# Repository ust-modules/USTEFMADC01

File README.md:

# EFMADC01 - Electric Field Mill ADC Module

The **EFMADC01** module is designed to provide an **analog front-end** and **ADC conversion** for [Electric Field Mill sensor](https://github.com/UniversalScientificTechnologies/THUNDERMILL01) development and experiments. It processes analog signals from the field mill electrodes and converts them into digital data for further processing.

## Features

- **High-Precision ADC**: Utilizes the **LTC1865** 16-bit, 250ksps analog-to-digital converter.
- **Low-Noise Analog Front End**: Incorporates **OPA314** operational amplifiers for signal conditioning.
- **Precision and stable Voltage Reference**: Includes a **1.25V reference** for accurate ADC operation.
- **Flexible Power Supply**: Supports **3.3V to 5V** operation.
- **RF Shielding**: Equipped with shielding to reduce external interference.
- **MCX Connector Input**: Enables high-quality signal connection.

## Functional Description

The **EFMADC01** module consists of three main blocks:

1. **Analog Front End (AFE)**:
   - Uses **OPA314** operational amplifiers for signal buffering and amplification.
   - High-impedance resistor (10MΩ) allows direct signal acquisition from the field mill sensor electrodes.

2. **ADC Conversion**:
   - **LTC1865-MS** ADC provides **16-bit resolution** with **250ksps sampling rate**.
   - Accepts differential input signals and supports SPI communication.

3. **Power and Reference**:
   - Powered by an external **3.3V or 5V** supply.
   - Features a **BZV55C-6.2V** Zener diode for overvoltage protection.
   - Uses a **1.25V precision voltage reference** for ADC stability.

## Hardware Connections

### Power Supply:
- **VCC**: Accepts **3.3V to 5V** input.
- **GNDA** and **GND**: Ground connections.

### Analog Input:
- **J9 (MCX Connector)**: Main analog signal input.
- **Operational amplifier stage** conditions the signal before ADC conversion.

## Typical Application

The **EFMADC01** module is primarily used in electric field mill experiments to measure atmospheric electric fields. It can also be employed in low-frequency scientific measurements where high-resolution ADC conversion is required.

## Schematic

For detailed circuit information, please take a look at the [EFMADC01 schematic](/doc/gen/EFMADC01-schematic.pdf) in the documentation.

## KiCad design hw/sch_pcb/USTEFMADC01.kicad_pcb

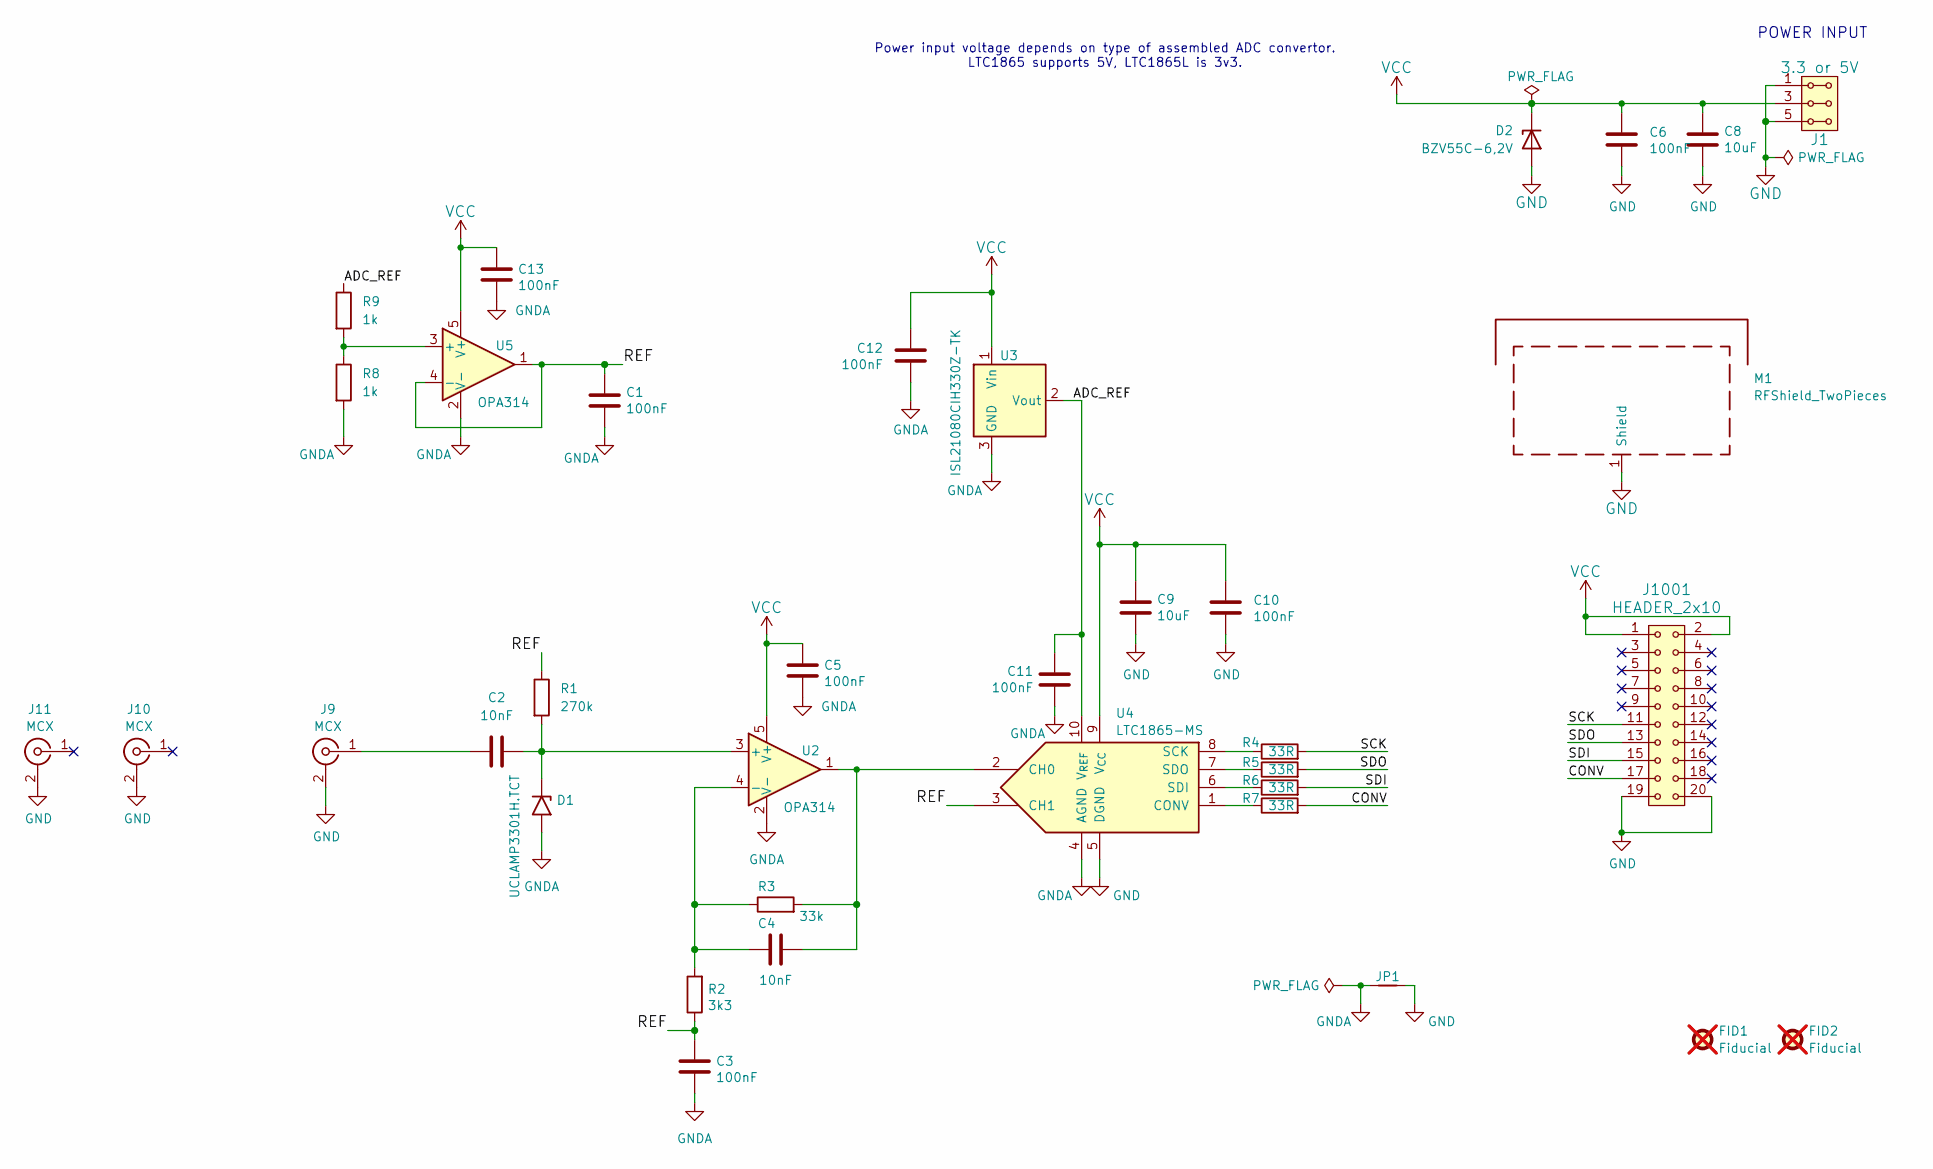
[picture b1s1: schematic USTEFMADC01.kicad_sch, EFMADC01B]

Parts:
C1, C3, C5, C6, C10, C11, C12, C13: 100nF; C_0805_2012Metric
C2, C4: 10nF; C_0805_2012Metric
C8, C9: 10uF; C_0805_2012Metric
D1: UCLAMP3301H.TCT; D_SMB
D2: BZV55C-6,2V; D_MiniMELF
FID1, FID2: Fiducial; Fiducial_1mm_Mask2mm; not fitted
J1: 3.3 or 5V; Straight_2x03
J9, J10, J11: MCX; SMA_Amphenol_901-144_Vertical
J1001: HEADER_2x10; Straight_2x10
JP1: Jumper_2_Bridged; NetTie-2_SMD_Pad0.5mm
M1: RFShield_TwoPieces; Laird_Technologies_BMI-S-204-F_32.00x32.00mm
R1: 270k; R_0805_2012Metric
R2: 3k3; R_0805_2012Metric
R3: 33k; R_0805_2012Metric
R4, R5, R6, R7: 33R; R_0805_2012Metric
R8, R9: 1k; R_0805_2012Metric
U2, U5: OPA314; SOT-23-5
U3: ISL21080CIH330Z-TK; SOT-23
U4: LTC1865-MS; MSOP-10_3x3mm_P0.5mm

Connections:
/ADC_REF: C11.1, R9.1, U3.2 (Vout), U4.10 (V_{REF})
/CONV: J1001.17, R7.2
/REF: C1.1, C3.2, R1.1, R2.1, U4.3 (CH1), U5.1, U5.4 (-)
/SCK: J1001.11, R4.2
/SDI: J1001.15, R6.2
/SDO: J1001.13, R5.2
GND: C6.2, C8.2, C9.2, C10.2, D2.2 (A), J1.1, J1.2, J1.5, J1.6, J9.2 (Ext), J10.2 (Ext_2), J11.2 (Ext_2), J1001.19, J1001.20, JP1.2, M1.1 (Shield_1), U4.5 (DGND)
GNDA: C1.2, C3.1, C5.1, C11.2, C12.2, C13.1, D1.2 (A2), JP1.1, R8.2, U2.2 (V-), U3.3 (GND), U4.4 (AGND), U5.2 (V-)
unnamed: C2.2, D1.1 (A1), R1.2, U2.3 (+)
unnamed: C2.1, J9.1 (In)
unnamed: C4.1, R2.2, R3.1, U2.4 (-)
unnamed: C4.2, R3.2, U2.1, U4.2 (CH0)
unnamed: R7.1, U4.1 (CONV)
unnamed: R4.1, U4.8 (SCK)
unnamed: R6.1, U4.6 (SDI)
unnamed: R5.1, U4.7 (SDO)
unnamed: R8.1, R9.2, U5.3 (+)
VCC: C5.2, C6.1, C8.1, C9.1, C10.1, C12.1, C13.2, D2.1 (K), J1.3, J1.4, J1001.1, J1001.2, U2.5 (V+), U3.1 (Vin), U4.9 (V_{CC}), U5.5 (V+)

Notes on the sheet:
Power input voltage depends on type of assembled ADC convertor. LTC1865 supports 5V, LTC1865L is 3v3.
POWER INPUT

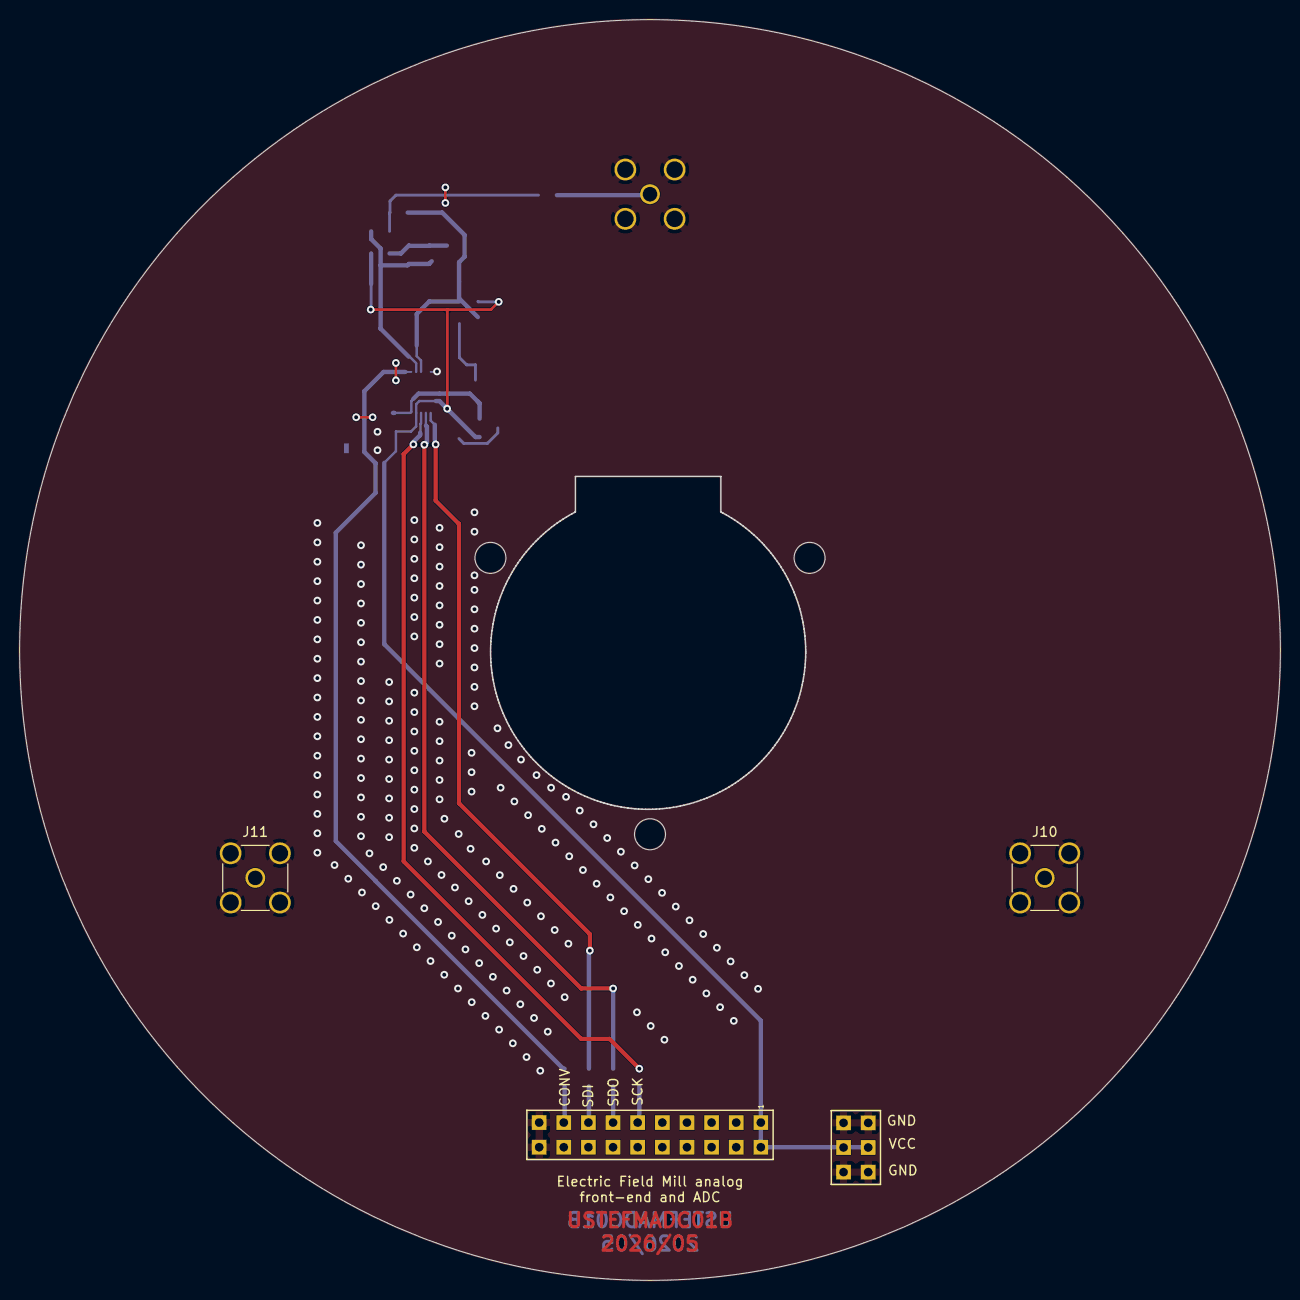
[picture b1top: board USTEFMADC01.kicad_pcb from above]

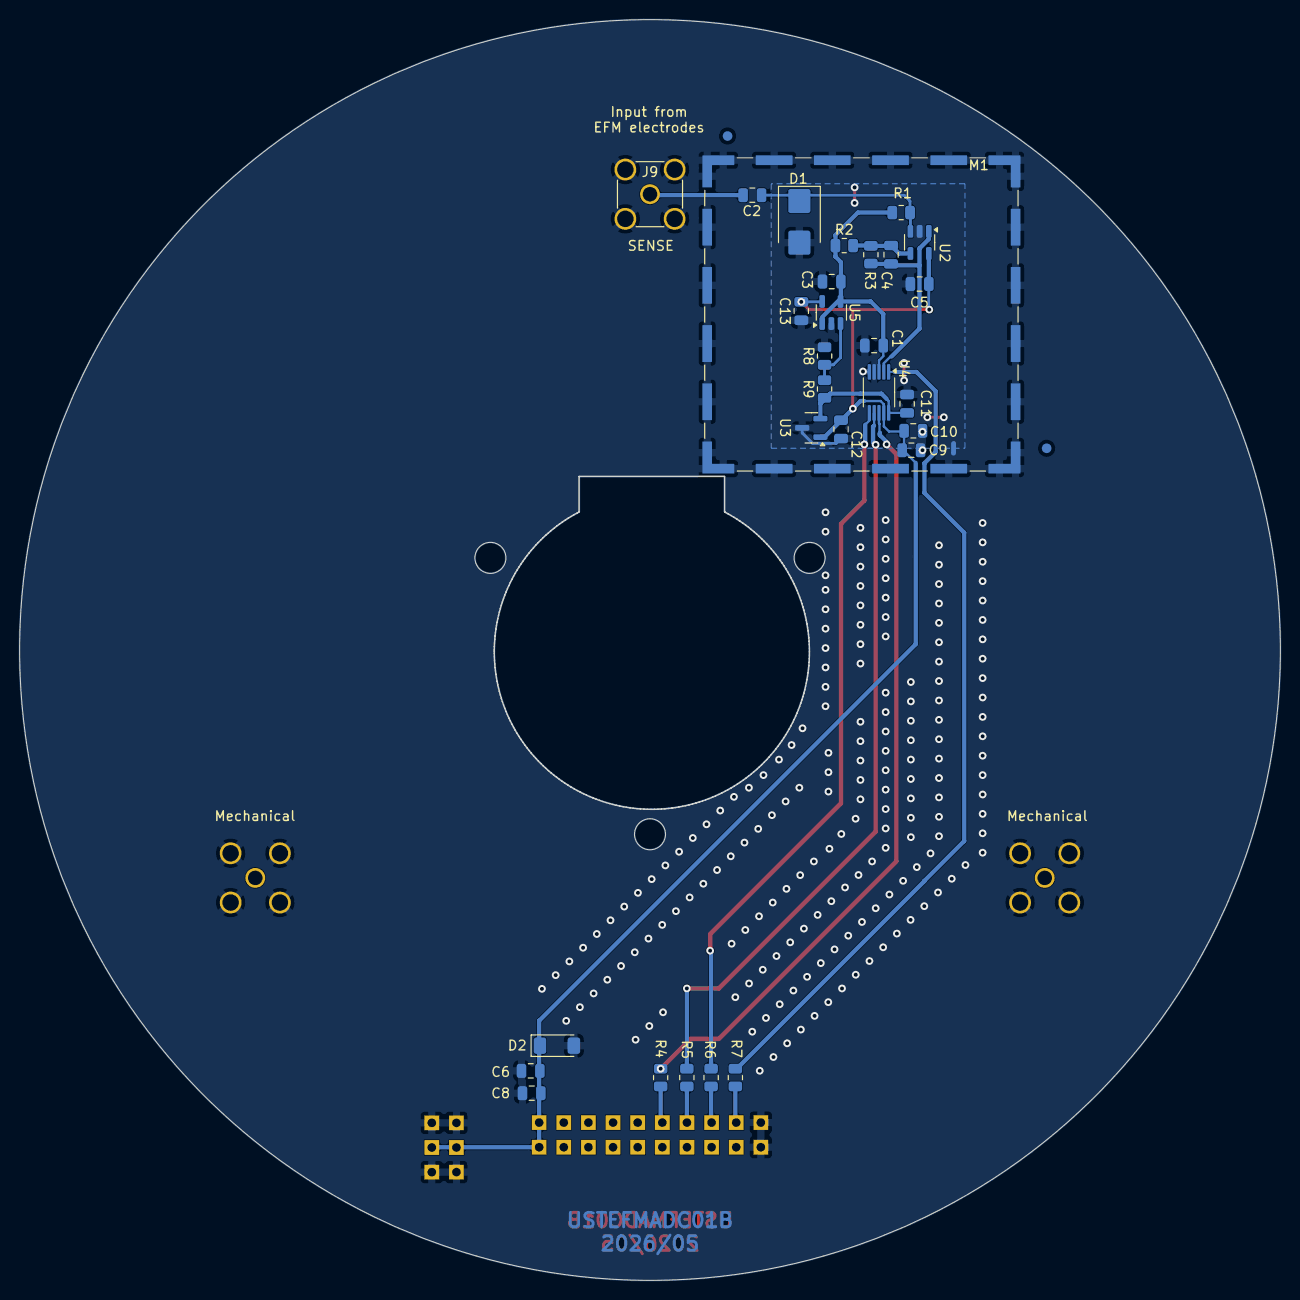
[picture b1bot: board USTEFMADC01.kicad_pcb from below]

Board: 2 copper layers, 129.9 x 129.9 mm, 36 parts (32 on the bottom side), 18 nets.

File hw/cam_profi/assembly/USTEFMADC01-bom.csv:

Component,Description,Part,References,Value,Footprint,Quantity Per PCB,Datasheet,ust_id
1,Unpolarized capacitor,C,C2C4,10nF,C_0805_2012Metric,2,,6508260b462c6d9e720541f1 5c70984812875079b91f8ba6
2,Unpolarized capacitor,C,C1C3C5C6C10C11C12C13,100nF,C_0805_2012Metric,8,,6508260b462c6d9e720541f1 5c70984712875079b91f8b4c
3,Unpolarized capacitor,C,C8C9,10uF,C_0805_2012Metric,2,,5c70984812875079b91f8bbe
4,Zener diode,D_Zener,D2,"BZV55C-6,2V",D_MiniMELF,1,,604b0326128750769e5b0f93
5,"600W unidirectional Transil Transient Voltage Suppressor, 12Vrwm, DO-214AA",SM6T12A,D1,UCLAMP3301H.TCT,D_SMB,1,https://www.st.com/resource/en/datasheet/sm6t.pdf,612514fe1287500165a976f3
6,2x10 2.54 mm pitch header,HEADER_2x10,J1001,HEADER_2x10,Straight_2x10,1,,
7,"coaxial connector (BNC, SMA, SMB, SMC, Cinch/RCA, LEMO, ...)",Conn_Coaxial,J9J10J11,MCX,SMA_Amphenol_901-144_Vertical,3,,5fa10cc512875025b39779f6
8,Two-piece EMI RF shielding cabinet,RFShield_TwoPieces,M1,RFShield_TwoPieces,Laird_Technologies_BMI-S-204-F_32.00x32.00mm,1,,5c72751c1287500b4e11301a
9,Resistor,R,R4R5R6R7,33R,R_0805_2012Metric,4,,5c70984512875079b91f8970
10,Resistor,R,R8R9,1k,R_0805_2012Metric,2,,5c70984712875079b91f8b6d
11,Resistor,R,R2,3k3,R_0805_2012Metric,1,,5c70984512875079b91f895e
12,Resistor,R,R3,33k,R_0805_2012Metric,1,,5c70984512875079b91f8962
13,Resistor,R,R1,270k,R_0805_2012Metric,1,,5c70984712875079b91f8b6d
14,"2.0V 25μA Micropower Voltage Reference, SOT-23",ISL21070CIH320Z-TK,U3,ISL21080CIH330Z-TK,SOT-23,1,http://www.intersil.com/content/dam/Intersil/documents/fn75/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,67d36d64ee7fc534862c3ebc
15,"Dual channel 16-bit SAR Analog to Digital Converter, 5V supply, 150ksps, SPI interface",LTC1865-MS,U4,LTC1865-MS,MSOP-10_3x3mm_P0.5mm,1,https://www.analog.com/media/en/technical-documentation/data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,651eae84462c6d9e7205573b
16,"50μV V OS, 0.25μV/°C, 35μA CMOS OPERATIONAL AMPLIFIERS, Zerø-Drift Series, SOT",OPA330xxDBV,U2U5,OPA314,SOT-23-5,2,http://www.ti.com/lit/ds/symlink/opa330.pdf,5c70984412875079b91f879a

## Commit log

2025-05-14 Update to actual state
2025-05-14 Update assets submodule to UST.
2025-05-14 update layout
2025-05-14 update actions
2025-05-14 rename souurce files
2025-05-14 Update actions products
2025-05-14 solve DRC issues
2025-05-15 Update workflow files
2026-04-19 Update README.md
    Fix image paths.
2026-05-29 Update to KiCAD 10. Fix component UST_IDs.
2026-06-25 Upadte to version 01B, update actions
2026-06-25 solve issues
2026-06-25 Remove accidentally tracked .history folder
